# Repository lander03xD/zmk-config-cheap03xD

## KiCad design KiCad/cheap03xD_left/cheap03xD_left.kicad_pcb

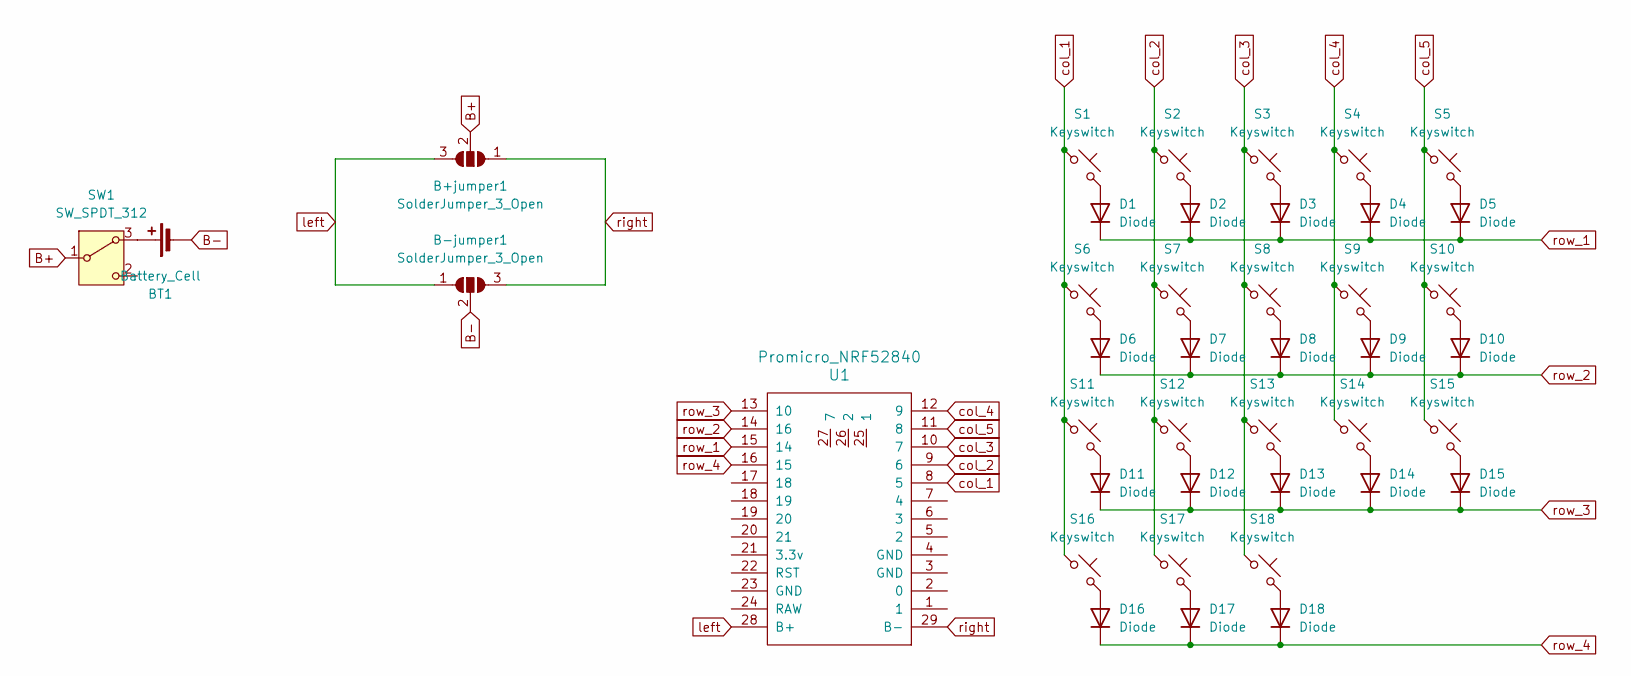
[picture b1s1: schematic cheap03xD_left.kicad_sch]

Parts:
B+jumper1: SolderJumper_3_Open; SolderJumper-3_P2.0mm_Open_TrianglePad1.0x1.5mm
B-jumper1: SolderJumper_3_Open; SolderJumper-3_P2.0mm_Open_TrianglePad1.0x1.5mm
BT1: Battery_Cell; SbM-9202_14250_battery_holder
D1, D2, D3, D4, D5, D6, D7, D8, D9, D10, D11, D12, D13, D14, D15, D16, D17, D18: Diode; Diode_DO-35
S1, S2, S3, S4, S5, S6, S7, S8, S9, S10, S11, S12, S13, S14, S15, S16, S17, S18: Keyswitch; Hotswap_MX_1.00u_reversible_18.5mm
SW1: SW_SPDT_312; SW_Vertical_Slide_5mm
U1: Promicro_NRF52840; Promicro_nrf52840

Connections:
B+: B+jumper1.2 (C), SW1.1 (B)
B-: B-jumper1.2 (C), BT1.2 (-)
unnamed: BT1.1 (+), SW1.3 (A)
unnamed: D1.2 (A), S1.2
unnamed: D2.2 (A), S2.2
unnamed: D3.2 (A), S3.2
unnamed: D4.2 (A), S4.2
unnamed: D5.2 (A), S5.2
unnamed: D6.2 (A), S6.2
unnamed: D7.2 (A), S7.2
unnamed: D8.2 (A), S8.2
unnamed: D9.2 (A), S9.2
unnamed: D10.2 (A), S10.2
unnamed: D11.2 (A), S11.2
unnamed: D12.2 (A), S12.2
unnamed: D13.2 (A), S13.2
unnamed: D14.2 (A), S14.2
unnamed: D15.2 (A), S15.2
unnamed: D16.2 (A), S16.2
unnamed: D17.2 (A), S17.2
unnamed: D18.2 (A), S18.2
col_1: S1.1, S6.1, S11.1, S16.1, U1.8 (5)
col_2: S2.1, S7.1, S12.1, S17.1, U1.9 (6)
col_3: S3.1, S8.1, S13.1, S18.1, U1.10 (7)
col_4: S4.1, S9.1, S14.1, U1.12 (9)
col_5: S5.1, S10.1, S15.1, U1.11 (8)
left: B+jumper1.3 (B), B-jumper1.1 (A), U1.28 (B+)
right: B+jumper1.1 (A), B-jumper1.3 (B), U1.29 (B-)
row_1: D1.1 (K), D2.1 (K), D3.1 (K), D4.1 (K), D5.1 (K), U1.15 (14)
row_2: D6.1 (K), D7.1 (K), D8.1 (K), D9.1 (K), D10.1 (K), U1.14 (16)
row_3: D11.1 (K), D12.1 (K), D13.1 (K), D14.1 (K), D15.1 (K), U1.13 (10)
row_4: D16.1 (K), D17.1 (K), D18.1 (K), U1.16 (15)

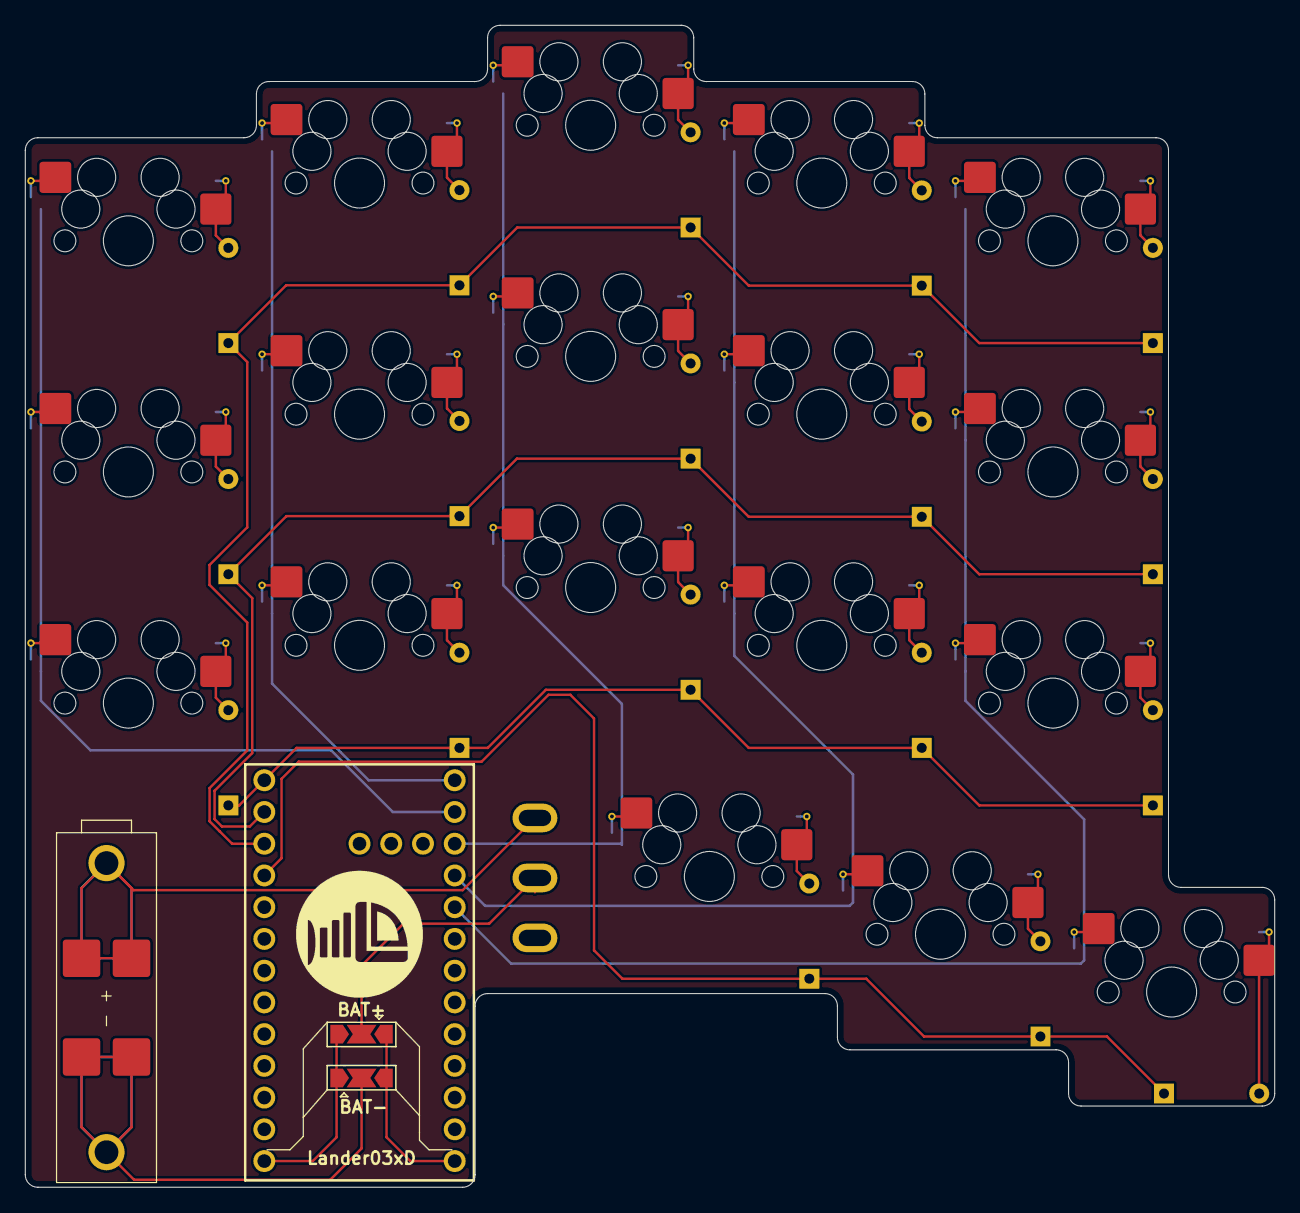
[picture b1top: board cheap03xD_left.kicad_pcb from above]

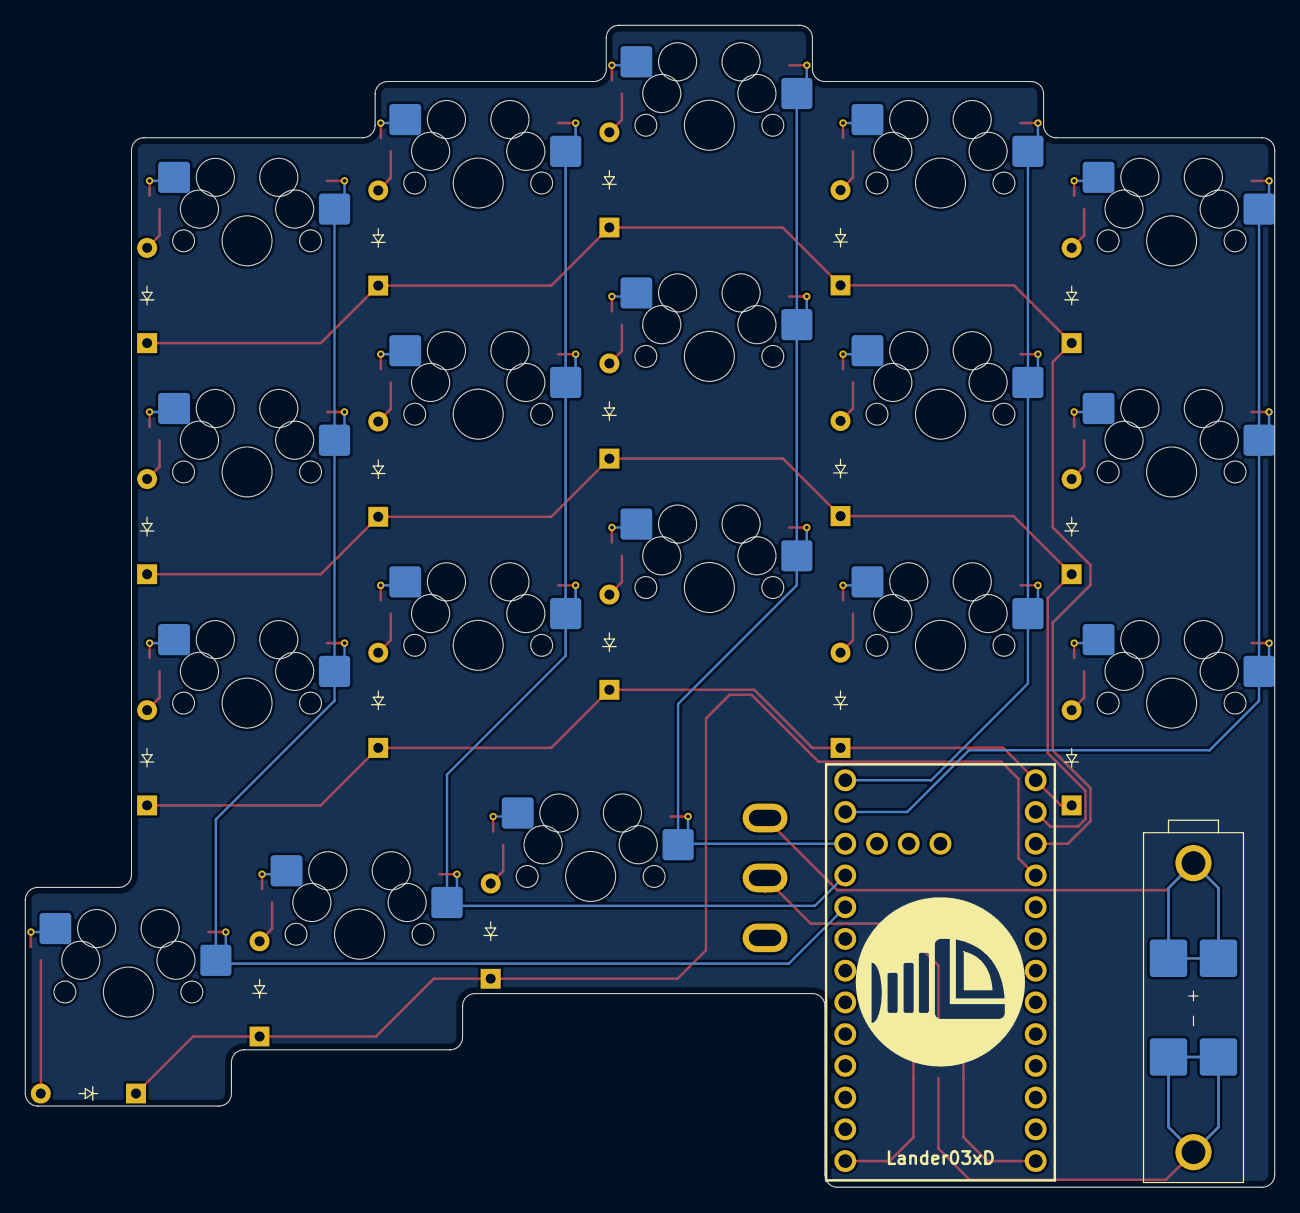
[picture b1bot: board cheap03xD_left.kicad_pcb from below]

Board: 2 copper layers, 100.0 x 93.0 mm, 41 parts (18 on the bottom side), 32 nets.

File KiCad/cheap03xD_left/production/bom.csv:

Designator,Footprint,Quantity,Value,LCSC Part #
BT1,SbM-9202_14250_battery_holder,1,Battery_Cell,
"D1, D10, D11, D12, D13, D14, D15, D16, D17, D18, D2, D3, D4, D5, D6, D7, D8, D9",Diode_DO-35,18,Diode,
"S1, S10, S11, S12, S13, S14, S15, S16, S17, S18, S2, S3, S4, S5, S6, S7, S8, S9",Hotswap_MX_1.00u_reversible_18.5mm,18,Keyswitch,
SW1,SW_Vertical_Slide_5mm,1,SW_SPDT_312,
U1,Promicro_nrf52840,1,Promicro_NRF52840,

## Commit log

2025-09-25 Initial User Config.
2025-09-25 correct some config
2025-09-25 flipped the columns on the left side
2025-10-16 cheap03xDv2
2025-10-16 fix right layout
2025-10-16 final ?
2025-10-19 freecad files
2025-10-19 kicad
2025-11-02 comb03xD
2025-11-02 removed dvorak shit
2025-11-02 removed most of the combos
2025-11-02 fixed config
2025-11-08 correct keymap
2025-11-10 overlay for failed board
2025-11-10 added modifiers and symbols
2025-11-10 fixed one shot to sticky keys
2025-11-10 removed lazy
2025-11-10 changed sticky key behavior
2025-11-10 move &sk out
2025-11-11 removed combo + tapdance for a tapdance layer
2025-11-11 fixed unique node
2025-11-11 longer tapping term
2025-11-11 shorter tapping term
2025-11-11 changed poweruserusage for cheap03xD
2025-11-12 added silkscreen art
2025-11-13 undo double le
2025-11-13 changed keymap
2025-11-14 config
2025-12-09 added combo keys and tapdance
2025-12-09 deduplicated node names
2025-12-09 changed tapdance
2025-12-09 tapdance test
2025-12-09 combo dedup
2025-12-09 added caps
2025-12-09 ctrl keys added
2025-12-09 individual ctrl
2025-12-09 reduce timeout
2025-12-25 changed combos
